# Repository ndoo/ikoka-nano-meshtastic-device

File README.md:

# Ikoka Nano Meshtastic Device

A Meshtastic device based on the [Seeed Studio XIAO nRF52840](https://www.seeedstudio.com/Seeed-XIAO-BLE-nRF52840-p-5201.html) and EBYTE E22-XXXMXXS series LoRa modules. Pinout matches the [Meshtastic xiao_ble variant](https://github.com/meshtastic/firmware/tree/master/variants/xiao_ble).

The focus is on small size without an onboard display or buttons, meaning it must be used with [Meshtastic client software](https://meshtastic.org/docs/software/), or as a remote repeater managed with [remote node administration](https://meshtastic.org/docs/configuration/remote-admin/).

## Connectors

* USB-C for power and data
* Qwiic connector for I²C sensors
* Battery connectors (PicoBlade 1.25-2P)
* Solar connector (PicoBlade 1.25-2P, 4.45 to 6.45 V - BQ25100 charge IC)

## Libraries Used

* [SnapMagic E22-900M30S footprint & symbol](https://www.snapeda.com/parts/E22-900M30S/EBYTE/view-part/)
* [SparkFun KiCad Libraries](https://github.com/sparkfun/SparkFun-KiCad-Libraries)
* [SeeedStudio OPL KiCad Library](https://github.com/ndoo/OPL_Kicad_Library/tree/xiao-ble-symbols) (forked to add missing XIAO nRF5240 symbol)

## Building One

### Software Required

* The files were created in [KiCad](https://www.kicad.org/) 8
* Clone this git repository recursively, i.e. with `--recursive`

### Ordering PCBs

* Generate the production files
  * Install [kicad-jlcpcb-tools](https://github.com/Bouni/kicad-jlcpcb-tools)
  * Open the PCB file
  * Tools -> External Plugins -> JLCPCB Tools
  * Look over the Bill of Materials list and perform any substitutions required
  * Click Generate
* Order the PCBs
  * Use the Gerbers, BOM and CPL files in `jlcpcb/production_files`
  * Default 1.6mm 2-layer PCB settings should work well, this PCB passes DRC based on JLCPCB specifications (other than the silkscreen of XIAO module being clipped by the PCB edge)

### Ordering Components

* Check the exported BOM file in `jlcpcb/production_files`

### Assembling the PCB

I suggest PCBA, but I used handsoldering pads and all SMDs are 0603 or larger so can be hand-soldered.

1. Solder the SMD components
   * The larger (0805) capacitors go closer to the USB-C connector end of the PCB
2. Solder the connectors
3. Solder the XIAO BLE
   1. It helps to tin the BAT+ pad first, it will help ensure successful soldering through the back. Remove excess solder so that the pad is flat, otherwise the XIAO will not sit flush
   2. Solder one pad first then verify all pads and the battery hole are lined up well, adjust the alignment if necessary
   3. Solder one more pad diagonally opposite, double check the alignment of the pads
   4. Solder the rear hole that goes to the BAT+ pad
   5. Solder the rest of the pads
   6. Test that the XIAO is able to power up from the battery and that charging works (a yellow LED will light up if the battery is charging), you won't be able to access the BAT+ pad once the E22 module is soldered
4. Solder the E22-900M30S module

### Flashing Meshtastic Firmware

#### Pre-built Binaries (Unofficial)

1. [Custom Meshtastic builds web installer](https://mrekin.duckdns.org/flasher/)
2. Select your device -> Xiao BLE
3. Select firmware version -> Pick the latest release
4. Select update or reinstall -> Update device (usually works fine, but if Meshtastic does not start after a few seconds, wipe and reinstall)
5. Download UF2
6. Connect USB-C to PC, double-tap the reset button
7. Drop UF2 file into XIAO-SENSE USB volume

#### Building from Source

Follow the instructions at [meshtastic/firmware/variants/diy/xiao_ble/](https://github.com/meshtastic/firmware/tree/master/variants/diy/xiao_ble).

### Enclosure

A snap-fit 3D printable enclosure is available in the `enclosures` folder. **This has not been updated for the latest board design ([2b17a53](https://github.com/ndoo/ikoka-nano-meshtastic-device/commit/2b17a53b4cfc0f9a9a845ffaf8d8353723f1d552)).**

## PCB Images

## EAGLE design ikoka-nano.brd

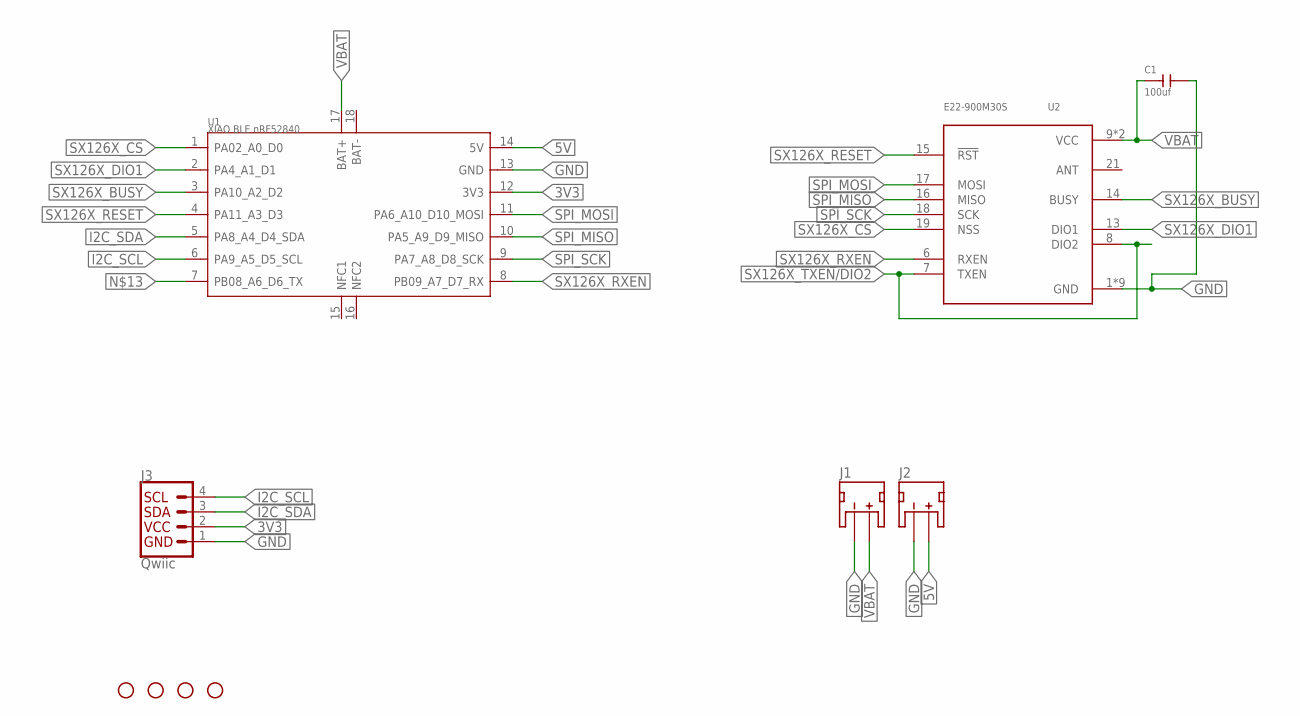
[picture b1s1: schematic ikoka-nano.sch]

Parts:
C1: 100uf; C1206
H1, H2, H3, H4: STAND-OFF
J1: LiPo 1S; JST-2-SMD
J2: Solar ≤6.45V; JST-2-SMD
J3: Qwiic; JST04_1MM_RA
U1: XIAO BLE nRF52840; MOUDLE16P-SMD-2.54-21X17.8MM
U2: E22-900M30S; XCVR_E22-900M30S

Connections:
3V3: J3.2, U1.12 (3V3)
5V: J2.2 (+), U1.14 (5V)
GND: C1.2, J1.1 (-), J2.1 (-), J3.1, U1.13 (GND), U2.1 (GND), U2.2 (GND), U2.3 (GND), U2.4 (GND), U2.5 (GND), U2.11 (GND), U2.12 (GND), U2.20 (GND), U2.22 (GND)
I2C_SCL: J3.4, U1.6 (PA9_A5_D5_SCL)
I2C_SDA: J3.3, U1.5 (PA8_A4_D4_SDA)
SPI_MISO: U1.10 (PA5_A9_D9_MISO), U2.16 (MISO)
SPI_MOSI: U1.11 (PA6_A10_D10_MOSI), U2.17 (MOSI)
SPI_SCK: U1.9 (PA7_A8_D8_SCK), U2.18 (SCK)
SX126X_BUSY: U1.3 (PA10_A2_D2), U2.14 (BUSY)
SX126X_CS: U1.1 (PA02_A0_D0), U2.19 (NSS)
SX126X_DIO1: U1.2 (PA4_A1_D1), U2.13 (DIO1)
SX126X_RESET: U1.4 (PA11_A3_D3), U2.15 (!RST)
SX126X_RXEN: U1.8 (PB09_A7_D7_RX), U2.6 (RXEN)
SX126X_TXEN/DIO2: U2.7 (TXEN), U2.8 (DIO2)
VBAT: C1.1, J1.2 (+), U1.17 (BAT+), U2.9 (VCC), U2.10 (VCC)

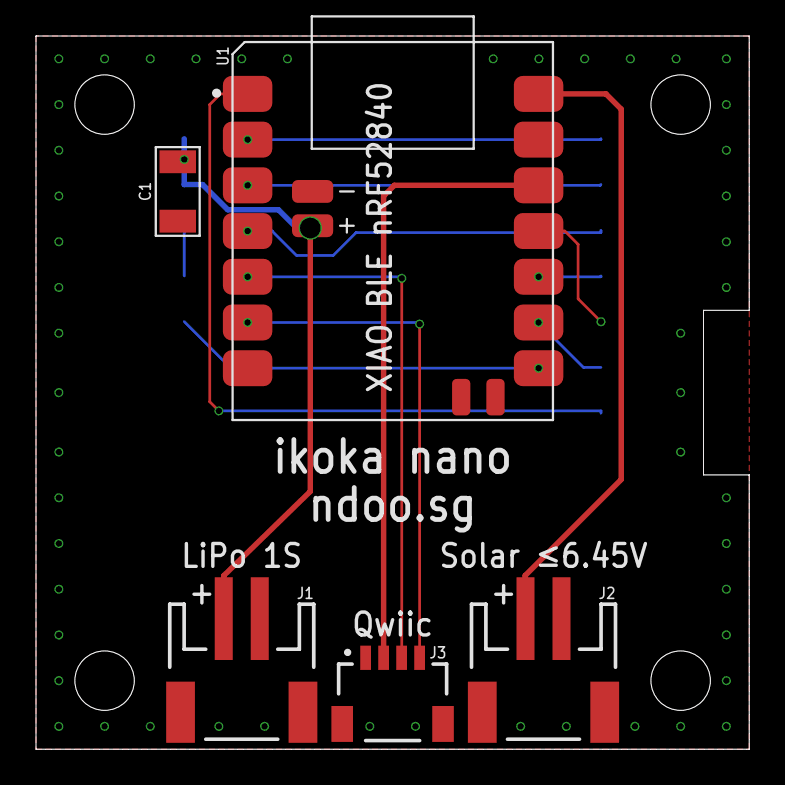
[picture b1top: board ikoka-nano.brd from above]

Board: 2 copper layers, 39.6 x 39.6 mm, 10 parts (1 on the bottom side), 15 nets.

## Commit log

2024-03-23 Update README.md with some build instructions and add CAM file
2024-03-23 Update README and add PCB images
2024-03-23 Redesign board because the E22-900M22S footprint from SnapMagic was much smaller than the actual module size; add solar 5V connector; reduce Qwiic connectors to just one.
2024-03-23 Move some values to names layer to ensure JLCPCB CAM generates silkscreen; hide U1/U2 value under components
2024-03-23 Update README.md with flashing instructions
2024-03-23 Add project name and ndoo.sg to board front
2024-03-23 Update PCB images
2024-03-23 Update schematic with LCSC part numbers
2024-03-23 Update board images to be non-perspective views
2024-03-23 Add generated Gerbers/BOM for JLCPCB
2024-05-09 Power EBYTE E22 module from 5V and remove JST-PH 2.0 connectors
    Power EBYTE E22 module from 5V because VBAT results in very poor transmit power.
    Remove JST connectors since the device no longer functions without 5V.
2024-05-09 Add kicad-render GitHub action
    Add kicad-render GitHub action from [linalinn/kicad-render](https://github.com/linalinn/kicad-render)
2024-05-09 Update README for KiCad 8 and rendered images
2024-05-09 Update footprints table
2024-05-09 Update .gitignore to ignore KiCad 8 lock files
2024-05-11 Update README.md and remove repo board images
2024-05-23 Update README to remove reference to battery and solar power.
2024-05-23 enclosure: Add 3D printable enclosure and update README
2024-05-23 Remove gerbers, use README instructions to generate them on demand
2024-11-28 Add LICENSE
2024-11-28 Add Molex Picoblade 1.25x2 connectors for VBAT and VBUS, add load switch for E22 module power
2024-11-28 Add missing D1 footprint and update PCB; add LCSC part numbers; remove gerbers
2024-11-28 Increase VBAT via size and add teardrop
2024-11-28 Fix part attributes for LCSC PN and make compatible with latest JLCPCB fabrication toolkit
2024-11-29 Add LCSC PN display for C1, clean up production folder again
2024-12-03 Sync submodules
2024-12-03 Branch Seeed OPL Kicad library to modify XIAO nRF52840 Library
2024-12-03 Update Seeed XIAO nRF52840 with BAT+ PTH pad
2024-12-10 Switch back to SparkFun Qwiic symbol/footprint, run DRC, fix 3D models
2024-12-10 Rebase XIAO BLE hand soldering symbol/footprint on upstream
2025-01-14 Add 5.4V boost converter circuit, use more JLCPCB basic parts, make PCB square, add internal battery connector
2025-01-14 Use AO3401A PMOS which is JLCPCB basic part
2025-02-27 Sync symbol libraries
2025-07-10 Add カモノハシのイコちゃん silkscreen
2025-07-10 chore: Sync footprint libraries
2025-07-10 chore(GitHub): Fix pcb_image workflow
2025-07-10 chore: Update .gitignore
2025-07-10 feat: Improve DC-DC converter and power path
    - Update R1 and R2 resistors to match Ikoka Handheld values (300kΩ, 39kΩ respectively)
    - Change E22 capacitors to 2x 47µF instead of 2x 100µF
    - Change P-MOSFET load switch to switch input to DC-DC boost so that E22 supply is constant even when switching to USB power
    - Add 300k pulldown on MT3608L enable pin to prevent it floating when Meshtastic firmware is not running
    - Layout for above changes
    - Move connectors flush with PCB edge
2025-07-10 chore: Use correct Kicad connector symbols and ground MountingPins
2025-07-10 fix(pcbnew): Set XIAO footprint type to SMD
2025-07-10 fix(pcbnew): XIAO 3dmodel path was incorrect
2025-07-13 Update README.md
    - Update "Assembling the PCB"
    - Update "Flashing Meshtastic Firmware" (fixes #10)
2025-07-15 feat: Improve boost converter part selection
    - Change inductor from 22uH FNR4026S220MT to 2.2uH FXL0420-2R2-M
    - Change MT3608L to MT3608B

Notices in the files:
parts and their libraries:
SparkFun-Connectors: Licensing: Creative Commons ShareAlike 4.0 International - https://creativecommons.org/licenses/by-sa/4.0
